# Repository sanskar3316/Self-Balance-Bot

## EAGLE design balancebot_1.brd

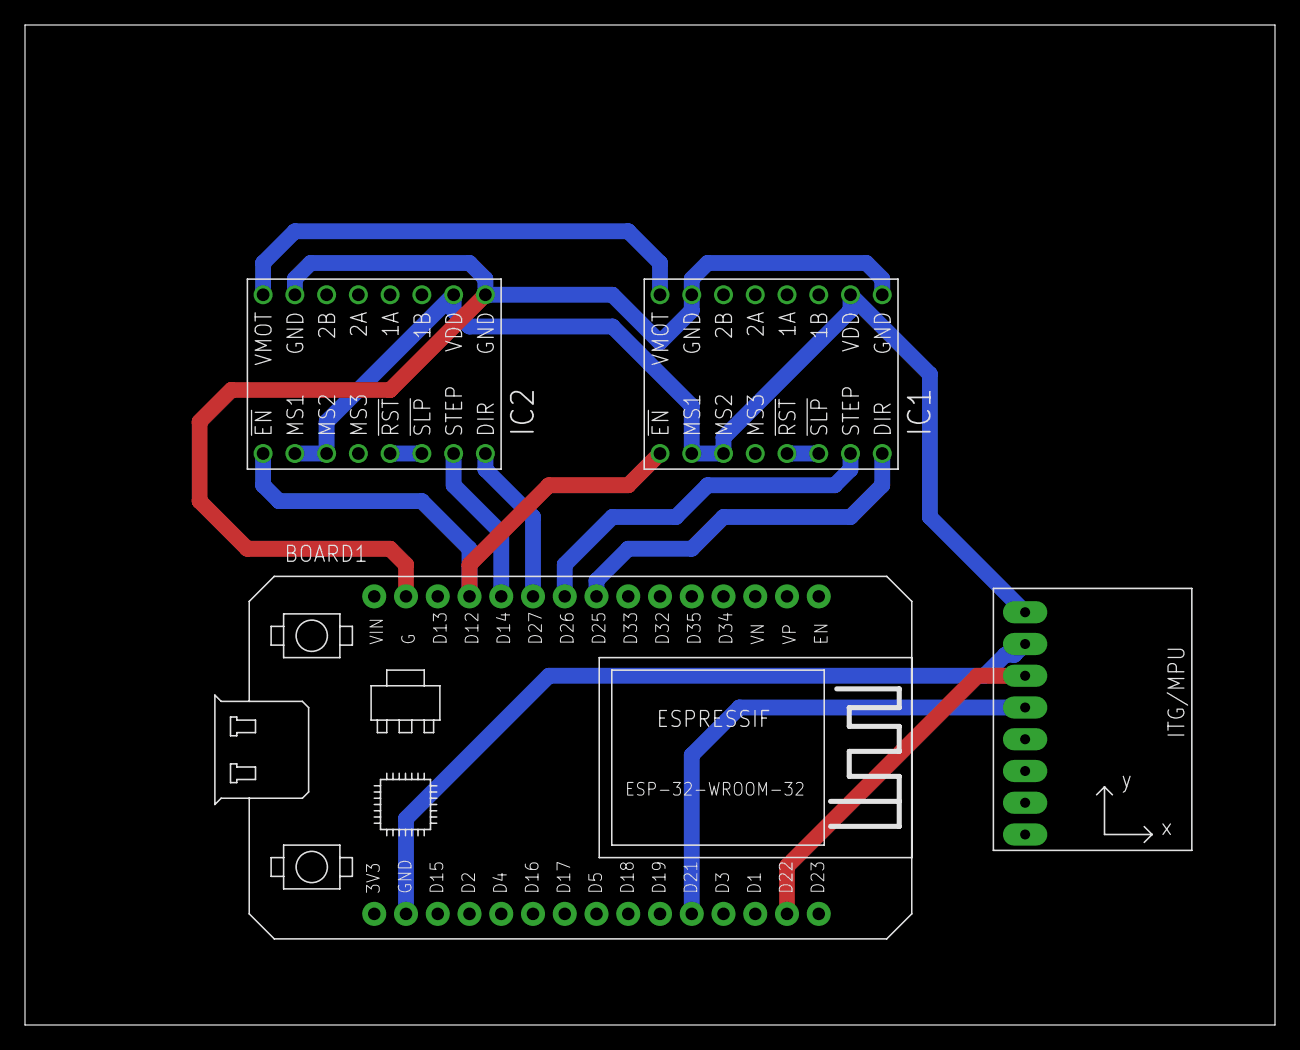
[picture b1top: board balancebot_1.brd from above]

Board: 2 copper layers, 100.0 x 80.0 mm, 4 parts (0 on the bottom side), 13 nets.

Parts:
BOARD1: ESP32DEVKITV1; ESP32-DEVKITV1
IC1, IC2: 1182-A4988; A4988
U1: GY-521MPU6050; GY-521

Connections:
unnamed: BOARD1.GND, IC1.9, IC1.15, IC2.9, IC2.15
unnamed: BOARD1.D12, IC1.1, IC2.1
unnamed: BOARD1.D14, IC2.7
unnamed: IC1.16, IC2.16
unnamed: BOARD1.D27, IC2.8
unnamed: BOARD1.D25, IC1.8
unnamed: BOARD1.D26, IC1.7
unnamed: IC1.2, IC1.3, IC1.10, IC2.2, IC2.3, IC2.10, U1.VCC
unnamed: IC1.5, IC1.6
unnamed: IC2.5, IC2.6
unnamed: BOARD1.GND@1, U1.GND
unnamed: BOARD1.D22, U1.SCL
unnamed: BOARD1.D21, U1.SDA
